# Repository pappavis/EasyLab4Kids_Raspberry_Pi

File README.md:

### EasyLab Arduino Robotauto
Arduino Robot alles-op-één bordje door **Michiel Erasmus** / EasyLab4Kids. Dit is die tegniese ontwerpe daarvan.<br/>

<br/>

Credits:
---
**Ontwerp** deur Michiel Erasmus<br/>
**Kontak** thebapodcast@gmail.com<br/>
**Voorbeelde** https://www.facebook.com/EasyBlocks4Kids/<br/>
<br/>

EasyLab basis
---
Wat maak die EasyLab so besonder?<br/>
 - Robotauto op die planeet **MARS!!**
 - Volledig praktyk getest op kinders in Nederland<br/>
 - Beskikbaar met online lesmateriaal in Zuid-Afrikaans en Nederlands<br/>
 
EasyLab tegniese moontlikhede
---
Vir mense met 'n computer brein..<br/>
 - Support vir 2x robotmotors<br/>
 - 1x servo aansluiting<br/>
 - 2x Lynvolg snesore aansluitinge
 - 7x koperplaat aansluiting om maklik 'goedkope' aliexpress-sensore te kan gebruik<br/>
 - Skroefverbindinge vir robotmotors<br/>
 - GPIO en IO-poorte is almal beskikbaar
 - Beskikbaar in twee smake: Arduino en Raspberry Pi<br/>
 <br/>
 Elke EasyLab wordt ambagtelik in Den Haag, Nederland gemaak deur personeel met 'n mentaal of fysieke beperking. Dit help mee aan 'n menswaardig bestaan.<br/>

Self probeer?
---
kyk dan op https://www.facebook.com/EasyBlocks4Kids/ <br/>
<br/>
**EasyLab4Kids met LCD skerm en afstandmeting sensor;**<br/>
<br/>
<br/>
**EasyLab nuusgierige by CoderDojo Den Haag, Nederland [Jun-2017]**<br/>
<br/>
<br/>
Wil jy ook 'n EasyLab? Kontak thebapodcast@gmail.com<br/>
<br/>
<br/>
#easylab4kids #easyblocks4kids #arduinorobot
<br/>

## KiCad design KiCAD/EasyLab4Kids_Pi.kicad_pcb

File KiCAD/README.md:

EasyLab: Raspberry Pi Edition
--
Dit is die printplaat ontwerp vir EasyLab pi editie.

**Credits:**<br/>
Ontwikkeld deur **Michiel Erasmus**.<br/>
Printplaat ontwerp deur **hemalchevli** op fiverr.com<br/>
<br/>
<br/>
**Copyrights**<br/>
GPLV2 license.<br/>
Noem my Michiel Erasmus in jouw credits.<br/>
<br/>
<br/>
<br/>
Printplaat;<br/>
<br/>
<br/>
#easylab4Kids #easyblocks4kids #erasmus-ict.nl #arduinorobot<br/>

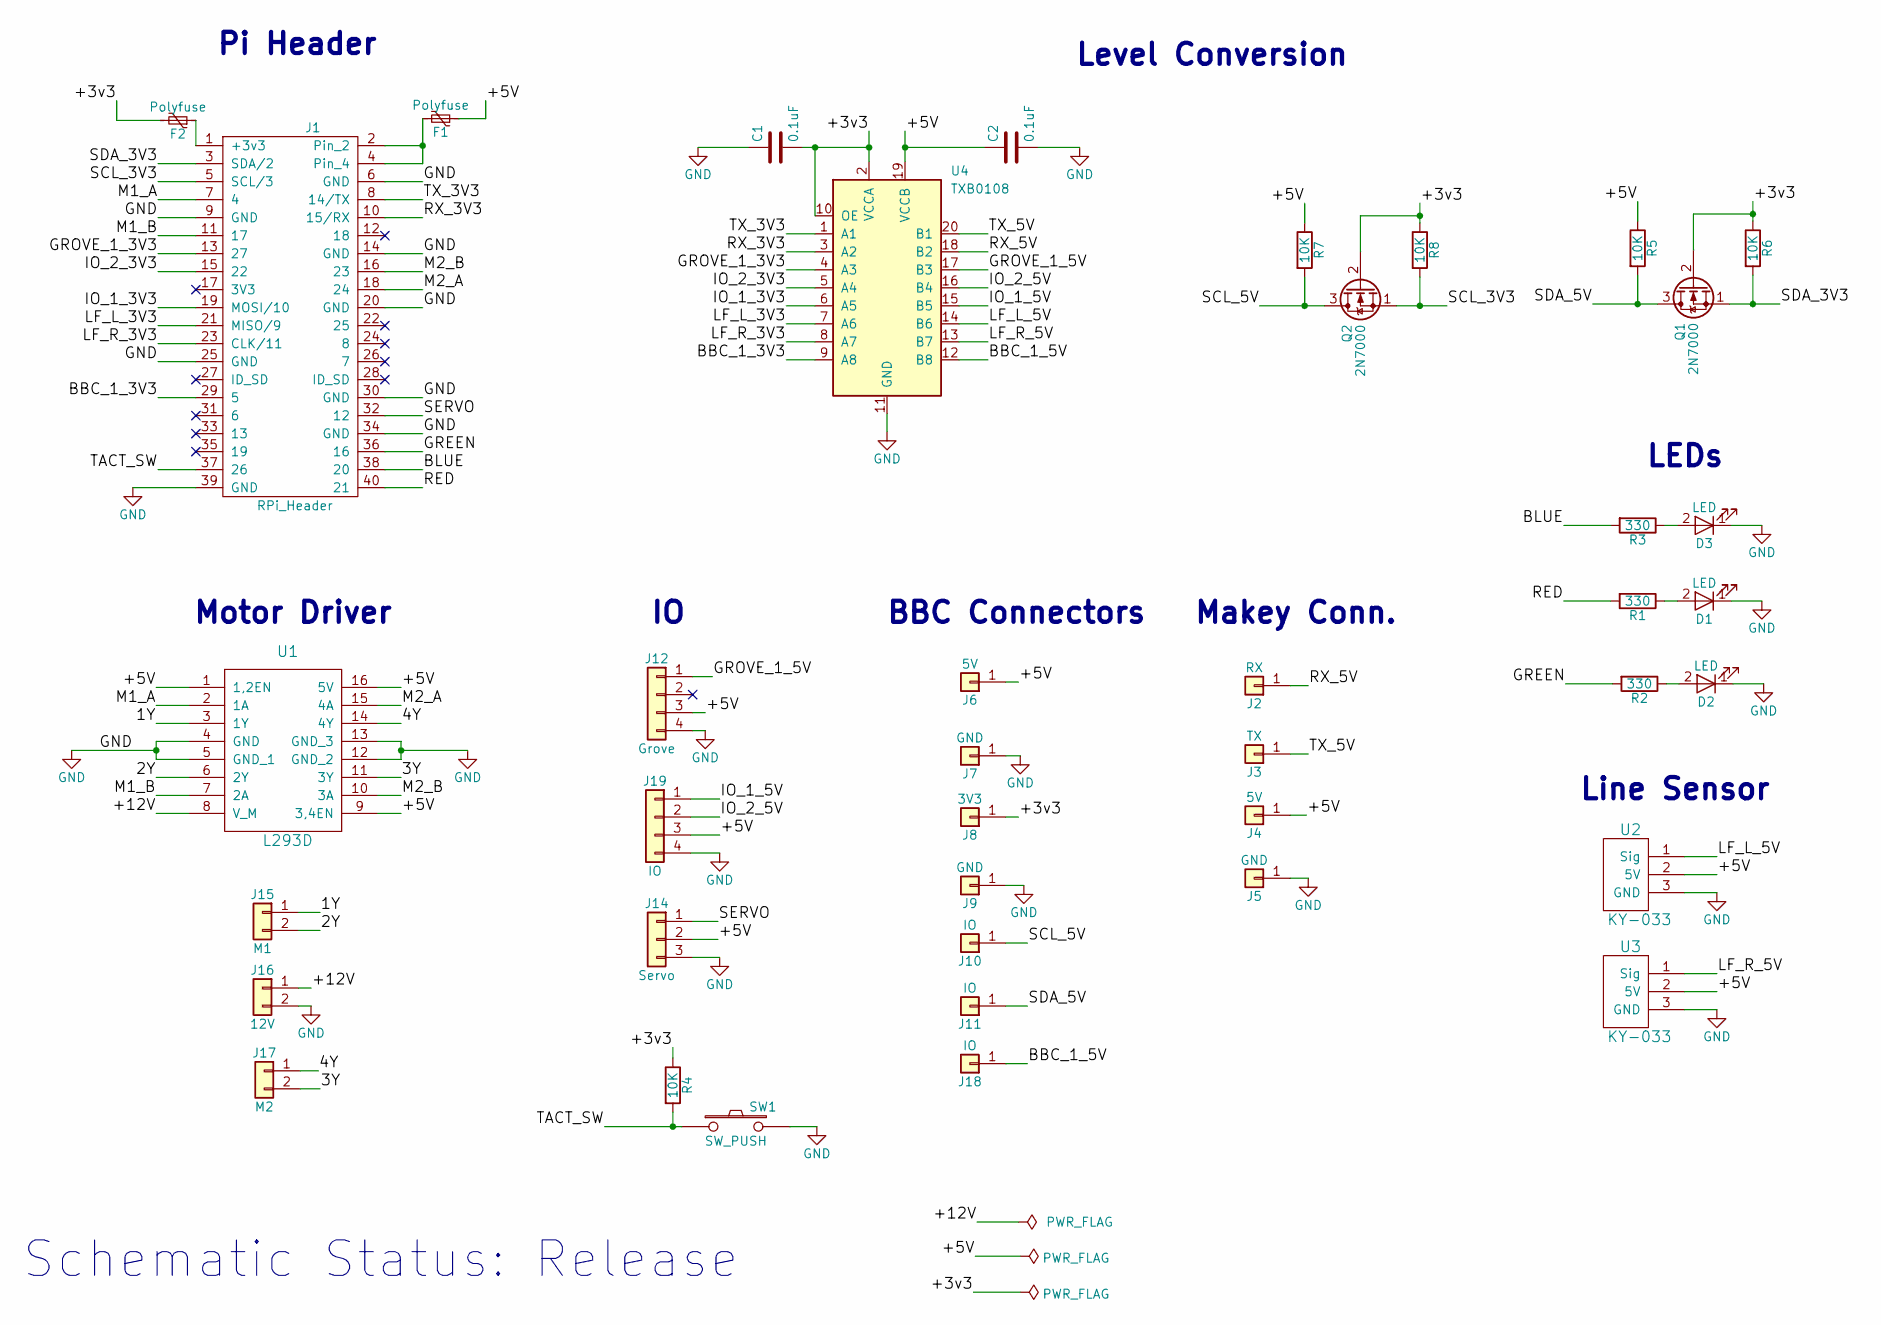
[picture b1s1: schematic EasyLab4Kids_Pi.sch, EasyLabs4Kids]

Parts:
C1, C2: 0.1uF; C_0805_HandSoldering
D1, D2, D3: LED; LED-5MM
F1, F2: Polyfuse; R_0805_HandSoldering
J1: RPi_Header; Pin_Header_Straight_2x20
J2: RX; Makey_conn
J3: TX; Makey_conn
J4: 5V; Makey_conn
J5: GND; Makey_conn
J6: 5V; BBC_CONNECTOR
J7, J9: GND; BBC_CONNECTOR
J8: 3V3; BBC_CONNECTOR
J10, J11, J18: IO; BBC_CONNECTOR
J12: Grove; grove_1x04
J14: Servo; Pin_Header_Straight_1x03
J15: M1; mkds_1,5-2
J16: 12V; mkds_1,5-2
J17: M2; mkds_1,5-2
J19: IO; Pin_Header_Straight_1x04
Q1, Q2: 2N7000; TO-92_Inline_Narrow_Oval
R1, R2, R3: 330; R_0805_HandSoldering
R4, R5, R6, R7, R8: 10K; R_0805_HandSoldering
SW1: SW_PUSH; PCB_PUSH_edit
U1: L293D; DIP-16_W7.62mm_LongPads
U2, U3: KY-033; Pin_Header_Straight_1x03
U4: TXB0108; SSOP-20_4.4x6.5mm_Pitch0.65mm

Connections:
/1Y: J15.1, U1.3 (1Y)
/2Y: J15.2, U1.6 (2Y)
/3Y: J17.2, U1.11 (3Y)
/4Y: J17.1, U1.14 (4Y)
/+3v3: C1.2, F2.2, J8.1, Q1.2 (G), Q2.2 (G), R4.1, R6.1, R8.1, U4.2 (VCCA), U4.10 (OE)
/+5V: C2.1, F1.1, J4.1, J6.1, J12.3, J14.2, J19.3, R5.1, R7.1, U1.1 (1,2EN), U1.9 (3,4EN), U1.16 (5V), U2.2 (5V), U3.2 (5V), U4.19 (VCCB)
/+12V: J16.1, U1.8 (V_M)
/BBC_1_3V3: J1.29 (5), U4.9 (A8)
/BBC_1_5V: J18.1, U4.12 (B8)
/BLUE: J1.38 (20), R3.2
/GREEN: J1.36 (16), R2.2
/GROVE_1_3V3: J1.13 (27), U4.4 (A3)
/GROVE_1_5V: J12.1, U4.17 (B3)
/IO_1_3V3: J1.19 (MOSI/10), U4.6 (A5)
/IO_1_5V: J19.1, U4.15 (B5)
/IO_2_3V3: J1.15 (22), U4.5 (A4)
/IO_2_5V: J19.2, U4.16 (B4)
/LF_L_3V3: J1.21 (MISO/9), U4.7 (A6)
/LF_L_5V: U2.1 (Sig), U4.14 (B6)
/LF_R_3V3: J1.23 (CLK/11), U4.8 (A7)
/LF_R_5V: U3.1 (Sig), U4.13 (B7)
/M1_A: J1.7 (4), U1.2 (1A)
/M1_B: J1.11 (17), U1.7 (2A)
/M2_A: J1.18 (24), U1.15 (4A)
/M2_B: J1.16 (23), U1.10 (3A)
/RED: J1.40 (21), R1.2
/RX_3V3: J1.10 (15/RX), U4.3 (A2)
/RX_5V: J2.1, U4.18 (B2)
/SCL_3V3: J1.5 (SCL/3), Q2.1 (S), R8.2
/SCL_5V: J10.1, Q2.3 (D), R7.2
/SDA_3V3: J1.3 (SDA/2), Q1.1 (S), R6.2
/SDA_5V: J11.1, Q1.3 (D), R5.2
/SERVO: J1.32 (12), J14.1
/TACT_SW: J1.37 (26), R4.2, SW1.1
/TX_3V3: J1.8 (14/TX), U4.1 (A1)
/TX_5V: J3.1, U4.20 (B1)
GND: C1.1, C2.2, D1.1 (K), D2.1 (K), D3.1 (K), J1.6 (GND), J1.9 (GND), J1.14 (GND), J1.20 (GND), J1.25 (GND), J1.30 (GND), J1.34 (GND), J1.39 (GND), J5.1, J7.1, J9.1, J12.4, J14.3, J16.2, J19.4, SW1.2, U1.4 (GND), U1.5 (GND_1), U1.12 (GND_2), U1.13 (GND_3), U2.3 (GND), U3.3 (GND), U4.11 (GND)
unnamed: D1.2 (A), R1.1
unnamed: D2.2 (A), R2.1
unnamed: D3.2 (A), R3.1
unnamed: F1.2, J1.2, J1.4
unnamed: F2.1, J1.1 (+3v3)

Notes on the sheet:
Schematic Status: Release
BBC Connectors
Motor Driver
Pi Header
Makey Conn.
Level Conversion
Line Sensor
LEDs

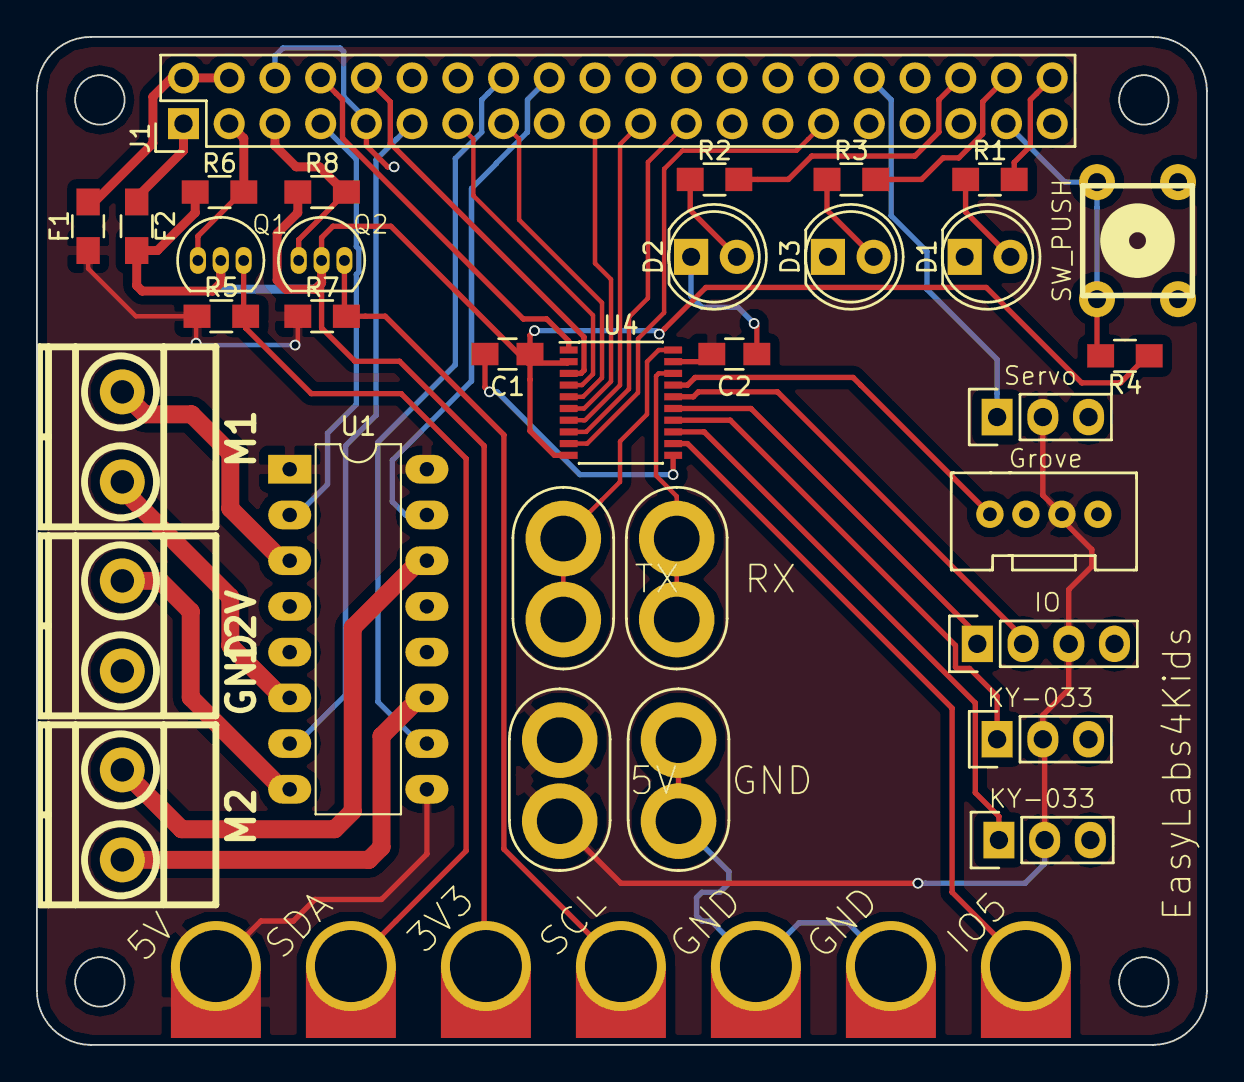
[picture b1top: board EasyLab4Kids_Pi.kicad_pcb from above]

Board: 2 copper layers, 65.0 x 56.0 mm, 40 parts (0 on the bottom side), 42 nets.

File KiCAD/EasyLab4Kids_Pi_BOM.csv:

Title,EasyLabs4Kids
Revision,0
Date,2017-09-21
Generated,11-1-2018 13:44:21
Company,
Comment 1,Drawn by Hemal C [from Fiverr]
Comment 2,
Comment 3,
Comment 4,
Total Parts,40
Total Unique Parts,26



Ref,Qty,Value,Footprint,MANF#,manf#,
C1 C2 ,2,0.1uF,EasyLab4Kids_Pi:C_0805_HandSoldering, , 
D3 D1 D2 ,3,LED,EasyLab4Kids_Pi:LED-5MM, , 
F1 ,1,Polyfuse,EasyLab4Kids_Pi:R_0805_HandSoldering,0ZCK0100FF2E, 
F2 ,1,Polyfuse,EasyLab4Kids_Pi:R_0805_HandSoldering, ,0ZCK0100FF2E
J6 ,1,5V,EasyLab4Kids_Pi:BBC_CONNECTOR, , 
J7 J9 ,2,GND,EasyLab4Kids_Pi:BBC_CONNECTOR, , 
J8 ,1,3V3,EasyLab4Kids_Pi:BBC_CONNECTOR, , 
J10 J11 J18 ,3,IO,EasyLab4Kids_Pi:BBC_CONNECTOR, , 
J15 ,1,M1,EasyLab4Kids_Pi:mkds_1,5-2, , 
J16 ,1,12V,EasyLab4Kids_Pi:mkds_1,5-2, , 
J17 ,1,M2,EasyLab4Kids_Pi:mkds_1,5-2, , 
J14 ,1,Servo,EasyLab4Kids_Pi:Pin_Header_Straight_1x03, , 
J2 ,1,RX,EasyLab4Kids_Pi:Makey_conn, , 
J3 ,1,TX,EasyLab4Kids_Pi:Makey_conn, , 
J4 ,1,5V,EasyLab4Kids_Pi:Makey_conn, , 
J5 ,1,GND,EasyLab4Kids_Pi:Makey_conn, , 
J1 ,1,RPi_Header,EasyLab4Kids_Pi:Pin_Header_Straight_2x20, , 
J12 ,1,Grove,EasyLab4Kids_Pi:grove_1x04, , 
J19 ,1,IO,EasyLab4Kids_Pi:Pin_Header_Straight_1x04, , 
Q2 Q1 ,2,2N7000,EasyLab4Kids_Pi:TO-92_Inline_Narrow_Oval, , 
R3 R1 R2 ,3,330,EasyLab4Kids_Pi:R_0805_HandSoldering, , 
R4 R7 R8 R5 R6 ,5,10K,EasyLab4Kids_Pi:R_0805_HandSoldering, , 
SW1 ,1,SW_PUSH,EasyLab4Kids_Pi:PCB_PUSH_edit, , 
U1 ,1,L293D,EasyLab4Kids_Pi:DIP-16_W7.62mm_LongPads, , 
U2 U3 ,2,KY-033,EasyLab4Kids_Pi:Pin_Header_Straight_1x03, , 
U4 ,1,TXB0108,EasyLab4Kids_Pi:SSOP-20_4.4x6.5mm_Pitch0.65mm, , 




BOM made with KICAD_BOM_WIZARD (https://github.com/HashDefineElectronics/KiCad_BOM_Wizard.git)
Generated 11-1-2018 13:44:21

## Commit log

2018-04-05 :confetti_ball: Added .gitattributes & .gitignore files
2018-04-05 eerste commit
2018-04-05 eerste
